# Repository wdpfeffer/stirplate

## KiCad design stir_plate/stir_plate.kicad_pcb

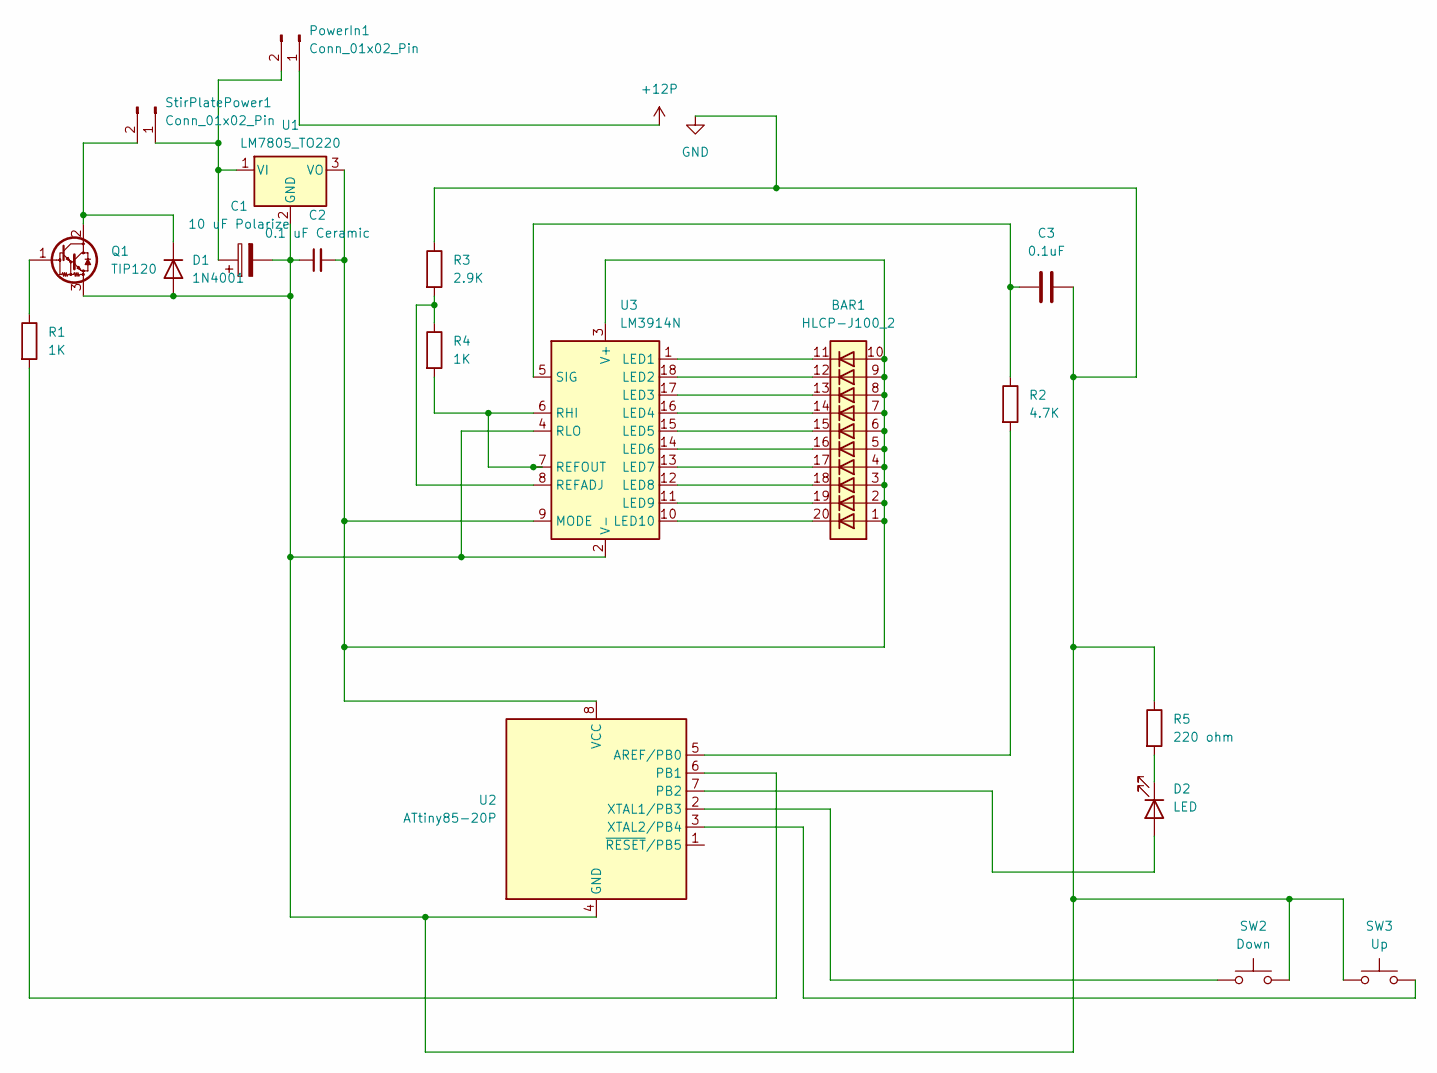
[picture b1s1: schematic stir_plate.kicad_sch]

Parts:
BAR1: HLCP-J100_2; HLCP-J100
C1: 10 uF Polarize; CP_Radial_Tantal_D4.5mm_P2.50mm
C2: 0.1 uF Ceramic; C_0805_2012Metric_Pad1.18x1.45mm_HandSolder
C3: 0.1uF; C_0805_2012Metric_Pad1.18x1.45mm_HandSolder
D1: 1N4001; D_DO-41_SOD81_P10.16mm_Horizontal
D2: LED; LED_D5.0mm
PowerIn1: Conn_01x02_Pin; PinHeader_1x02_P2.54mm_Vertical
Q1: TIP120; TO-220-3_Vertical
R1, R4: 1K; R_0805_2012Metric_Pad1.20x1.40mm_HandSolder
R2: 4.7K; R_0805_2012Metric_Pad1.20x1.40mm_HandSolder
R3: 2.9K; R_0805_2012Metric_Pad1.20x1.40mm_HandSolder
R5: 220 ohm; R_0805_2012Metric_Pad1.20x1.40mm_HandSolder
SW2: Down; SW_PUSH_6mm_H5mm
SW3: Up; SW_PUSH_6mm_H5mm
StirPlatePower1: Conn_01x02_Pin; PinHeader_1x02_P2.54mm_Vertical
U1: LM7805_TO220; TO-220-3_Vertical
U2: ATtiny85-20P; DIP-8_W7.62mm
U3: LM3914N; DIP-18_W7.62mm

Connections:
+12P: PowerIn1.1
GND: C1.2, C2.1, C3.2, D1.2 (A), Q1.3 (E), R3.1, R5.1, SW2.2, SW3.1, U1.2 (GND), U2.4 (GND), U3.2 (V-), U3.4 (RLO)
unnamed: D1.1 (K), Q1.2 (C), StirPlatePower1.2
unnamed: D2.2 (A), U2.7 (PB2)
unnamed: D2.1 (K), R5.2
unnamed: C1.1, PowerIn1.2, StirPlatePower1.1, U1.1 (VI)
unnamed: Q1.1 (B), R1.1
unnamed: BAR1.1 (A), BAR1.2 (A), BAR1.3 (A), BAR1.4 (A), BAR1.5 (A), BAR1.6 (A), BAR1.7 (A), BAR1.8 (A), BAR1.9 (A), BAR1.10 (A), C2.2, U1.3 (VO), U2.8 (VCC), U3.3 (V+), U3.9 (MODE)
unnamed: R2.2, U2.5 (AREF/PB0)
unnamed: R1.2, U2.6 (PB1)
unnamed: SW2.1, U2.2 (XTAL1/PB3)
unnamed: SW3.2, U2.3 (XTAL2/PB4)
unnamed: BAR1.11 (K), U3.1 (LED1)
unnamed: BAR1.12 (K), U3.18 (LED2)
unnamed: BAR1.13 (K), U3.17 (LED3)
unnamed: BAR1.14 (K), U3.16 (LED4)
unnamed: BAR1.15 (K), U3.15 (LED5)
unnamed: BAR1.16 (K), U3.14 (LED6)
unnamed: BAR1.17 (K), U3.13 (LED7)
unnamed: BAR1.18 (K), U3.12 (LED8)
unnamed: BAR1.19 (K), U3.11 (LED9)
unnamed: BAR1.20 (K), U3.10 (LED10)
unnamed: R3.2, R4.1, U3.8 (REFADJ)
unnamed: R4.2, U3.6 (RHI), U3.7 (REFOUT)
unnamed: C3.1, R2.1, U3.5 (SIG)

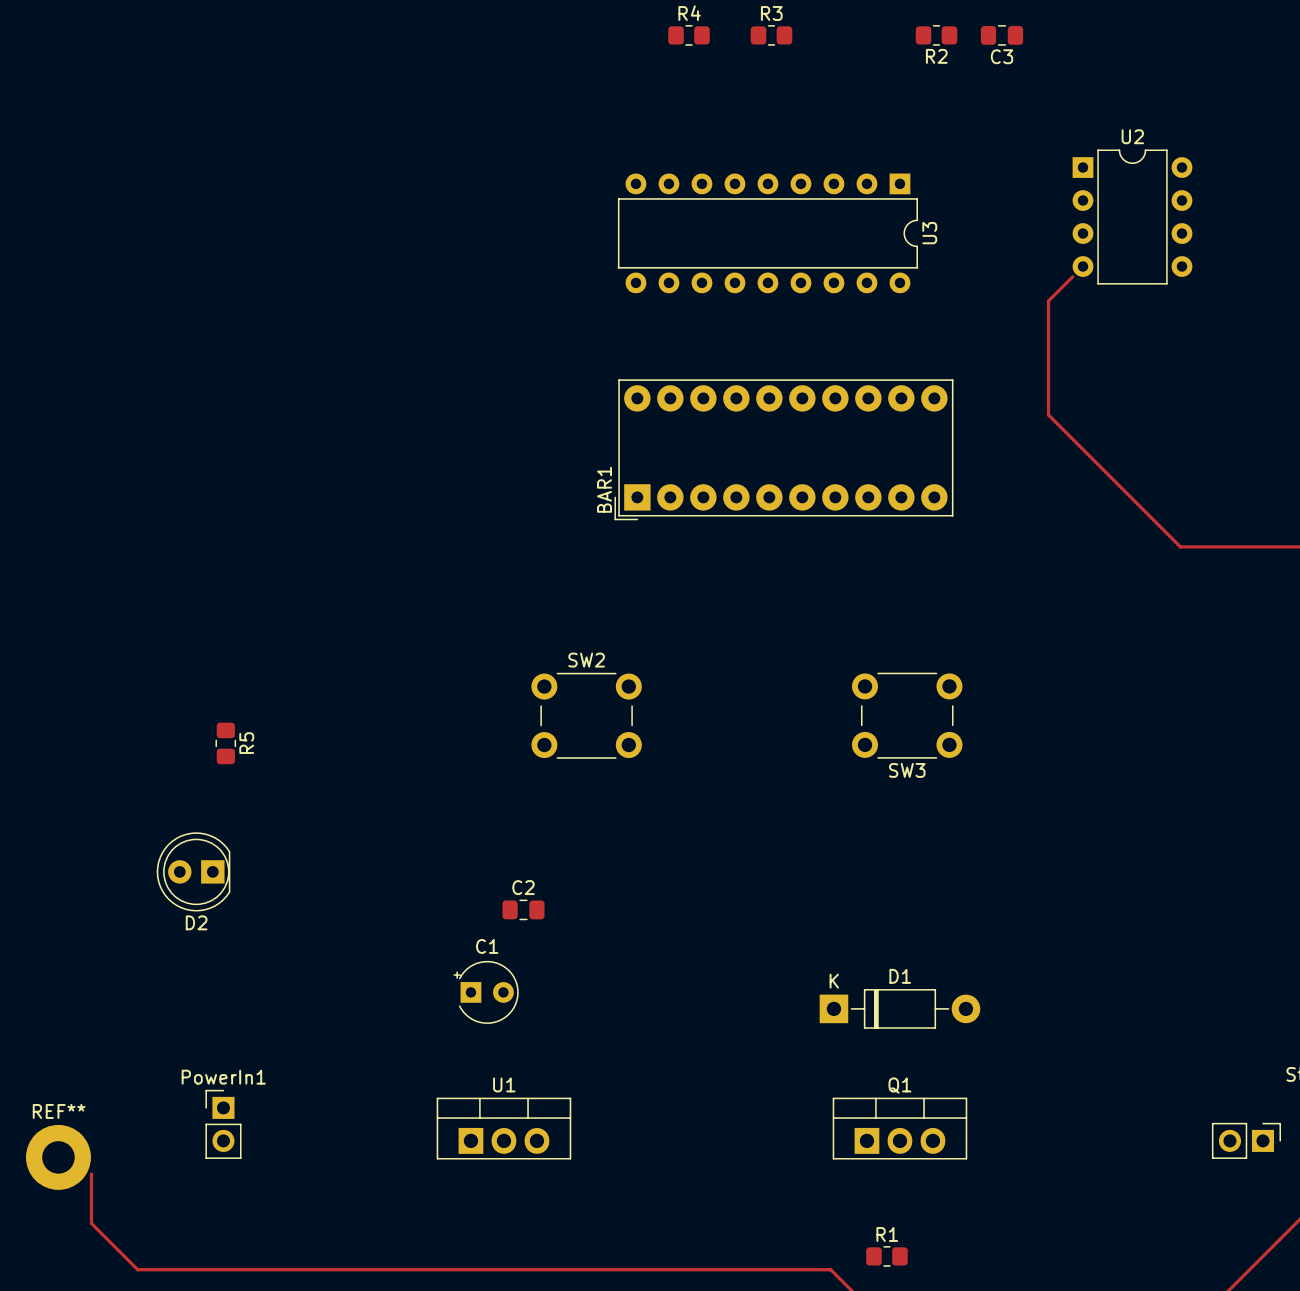
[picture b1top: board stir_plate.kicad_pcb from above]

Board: 2 copper layers, 19 parts (0 on the bottom side), 24 nets.

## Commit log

2023-06-06 first add
2023-08-03 updating files
